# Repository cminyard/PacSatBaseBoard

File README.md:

# PacSatBaseBoard

This is a base board design to start with for a PacSat design, or
really any Pumpkin Space CSKB board.

To use this, pull this project up in KiCad, then do "Save As" under
the file menu and save it in a new directory to use as the starting
point for your board.  You might have to deal with the .git directory
being copied.

All local footprints go into the "footprints" directory, create symbol
libraries in the "symbols" directory as necessary.  There are already
connectors added to those.

NOTE: The CSKB standard has ESQ-126-39-G-D PC104 connectors, which
have 12.19mm pins.  This leaves around 3mm of pin exposed between the
boards.  This design has ESQ-126-38-G-D PC104 connectors, which has
7.36mm pins.  This leaves the 11.05mm as the board height, and 11.11mm
(.438") spacers are pretty common.

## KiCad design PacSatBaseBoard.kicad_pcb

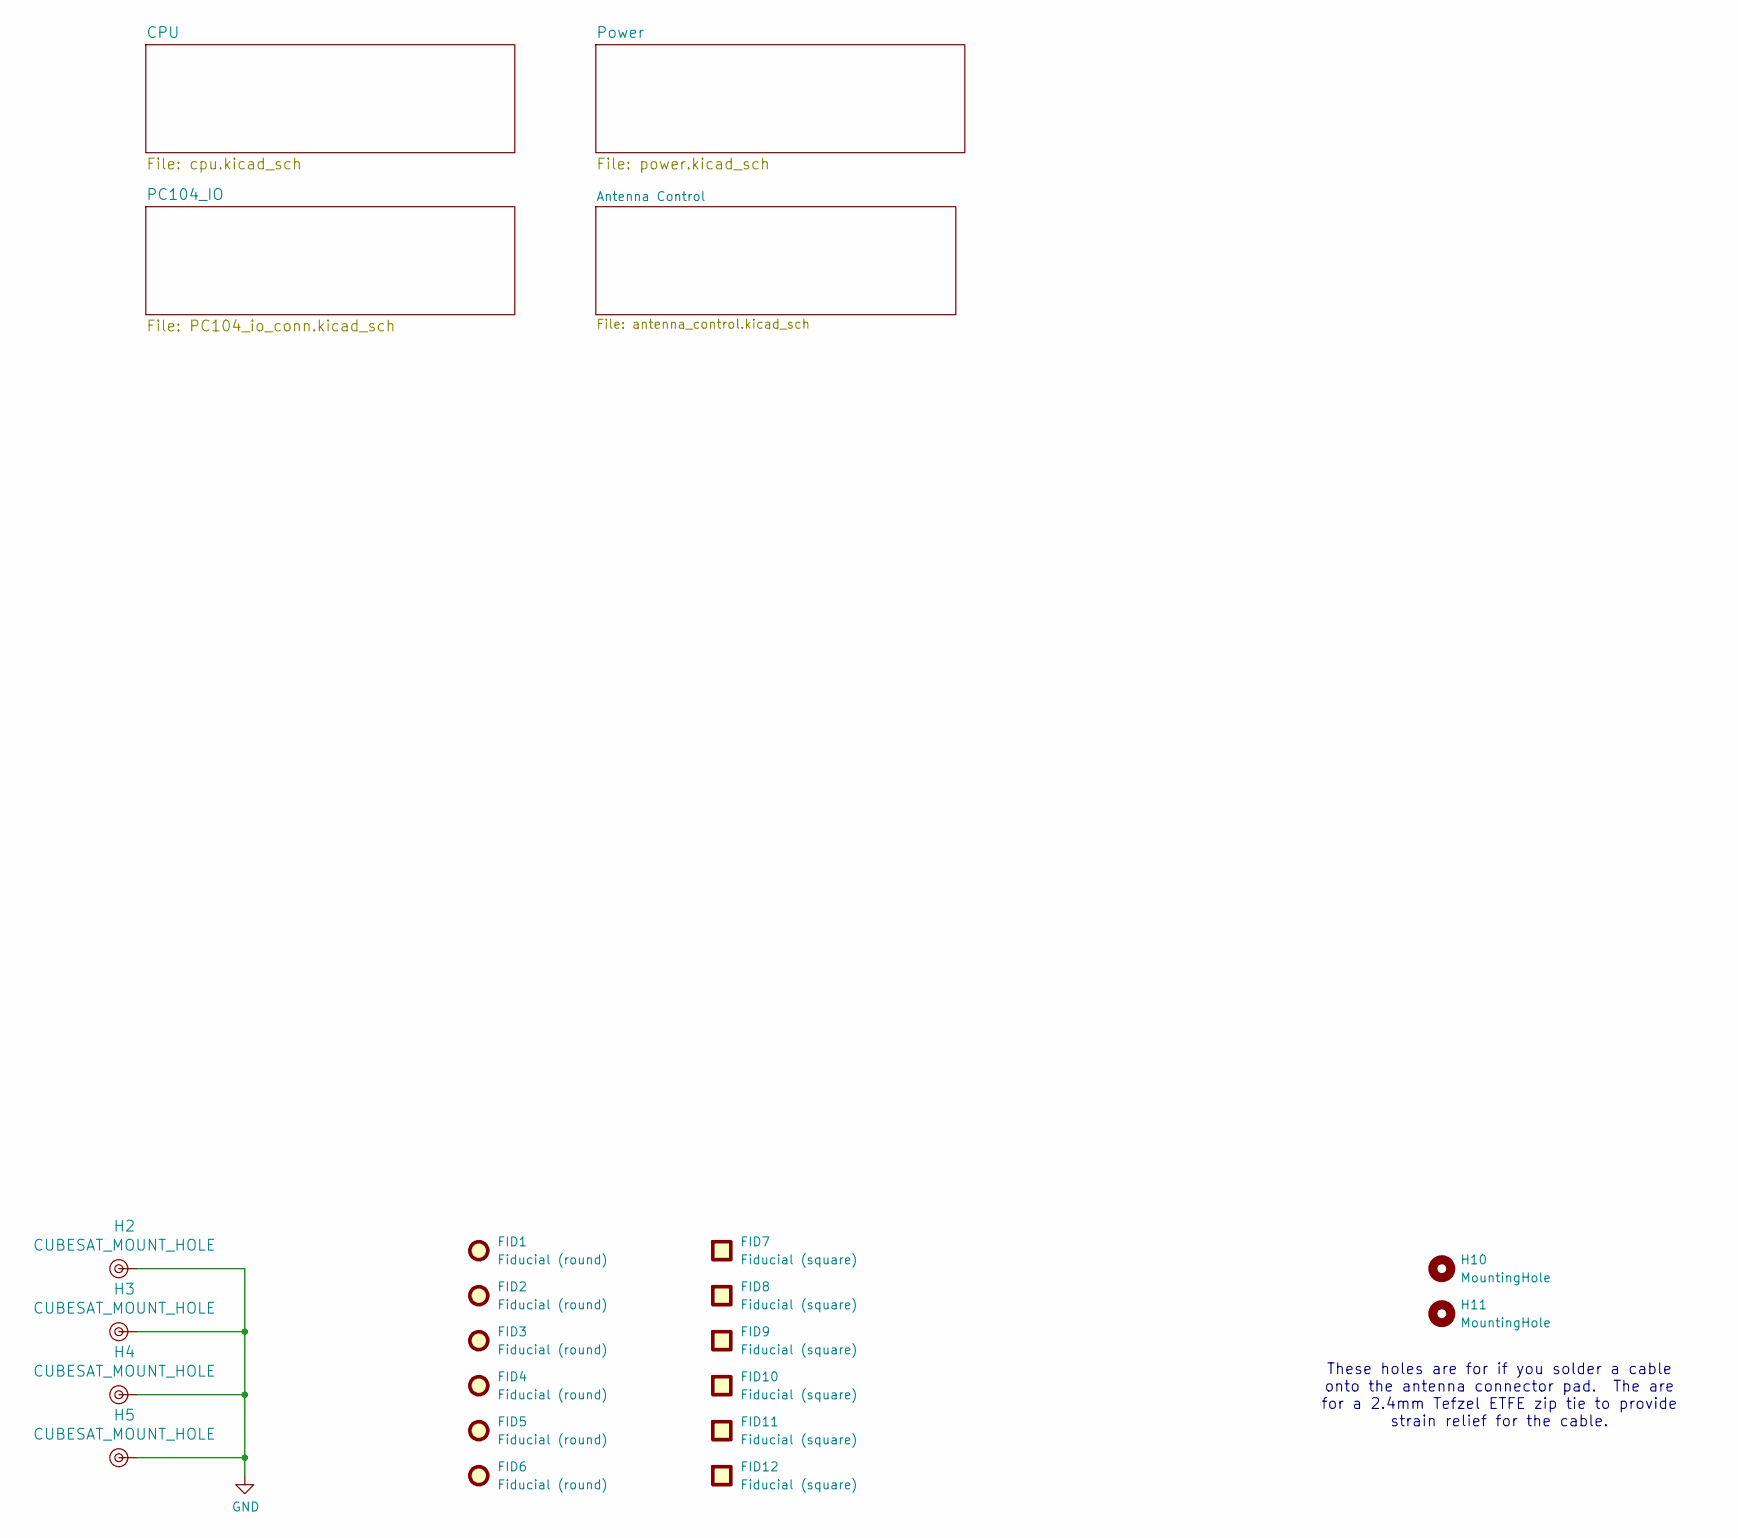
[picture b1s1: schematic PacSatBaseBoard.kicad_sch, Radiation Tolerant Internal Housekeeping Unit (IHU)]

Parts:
FID1, FID2, FID3, FID4, FID5, FID6: Fiducial (round); Fiducial_1mm_Mask2mm
FID7, FID8, FID9, FID10, FID11, FID12: Fiducial (square); Fiducial_Square_1mm_Mask2mm
H2, H3, H4, H5: CUBESAT_MOUNT_HOLE
H10, H11: MountingHole; MountingHole_2.7mm

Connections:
GND: H2.1, H3.1, H4.1, H5.1; also elsewhere on the board

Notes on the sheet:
These holes are for if you solder a cable onto the antenna connector pad. The are for a 2.4mm Tefzel ETFE zip tie to provide strain relief for the cable.

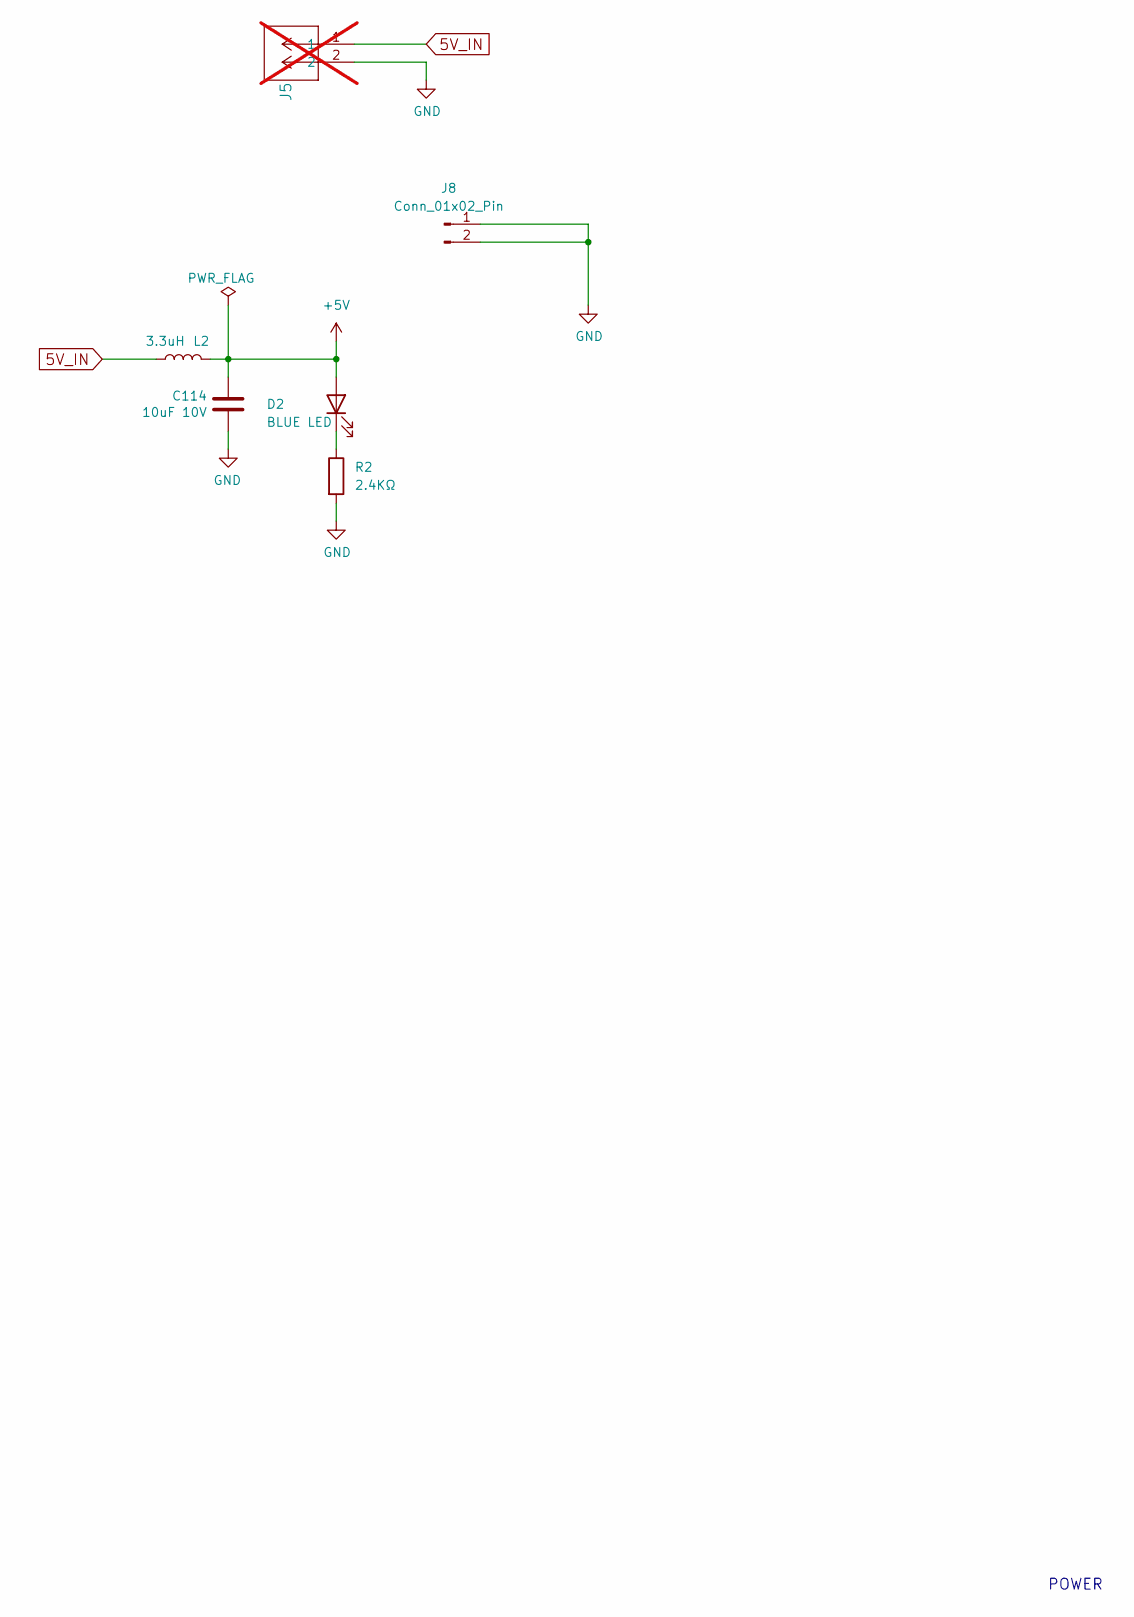
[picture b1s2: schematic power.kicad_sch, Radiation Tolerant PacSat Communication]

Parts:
C114: 10uF 10V; C_1206_3216Metric
D2: BLUE LED; LED_0603_1608Metric_Pad1.05x0.95mm_HandSolder
J5: HTSW-102-07-G-S; CON2_1X2_TU_TSW; not fitted
J8: Conn_01x02_Pin; SolderWire-0.5sqmm_1x02_P4.6mm_D0.9mm_OD2.1mm
L2: 3.3uH; L_1210_3225Metric_Pad1.42x2.65mm_HandSolder
R2: 2.4KΩ; R_0603_1608Metric_Pad0.98x0.95mm_HandSolder

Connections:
5V_IN: J5.1, L2.2; also elsewhere on the board
+5V: C114.1, D2.2 (A), L2.1
GND: C114.2, J5.2, J8.1, J8.2, R2.2; also elsewhere on the board
unnamed: D2.1 (K), R2.1

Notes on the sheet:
POWER

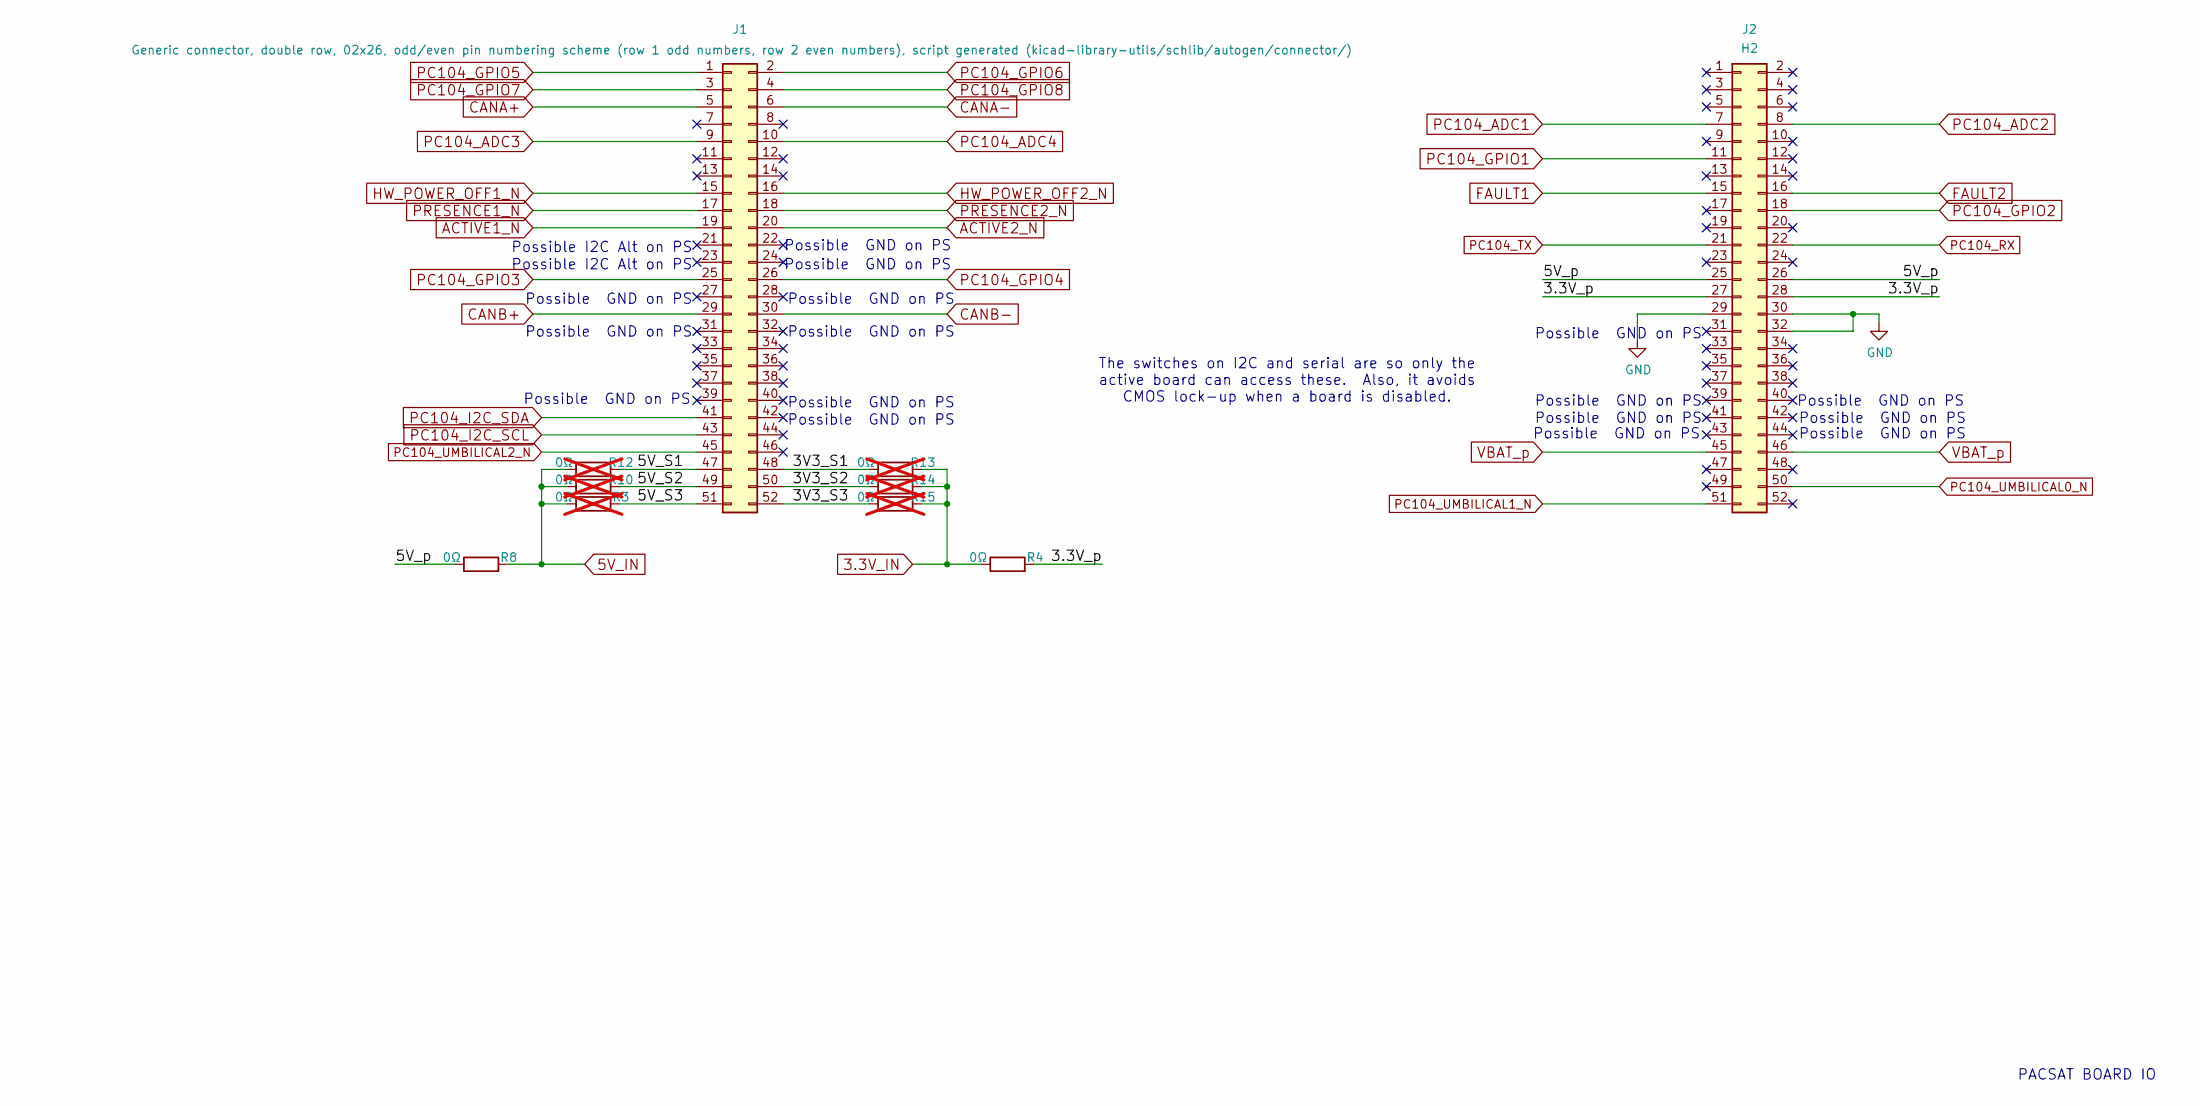
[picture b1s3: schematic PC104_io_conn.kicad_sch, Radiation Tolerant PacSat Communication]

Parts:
J1, J2: ESQ-126-38-G-D; CONN_ESQ-126-39-G-D_SAI
R3, R10, R12, R13, R14, R15: 0Ω; R_0603_1608Metric_Pad0.98x0.95mm_HandSolder; not fitted
R4, R8: 0Ω; R_0603_1608Metric_Pad0.98x0.95mm_HandSolder

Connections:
3.3V_IN: R4.1, R13.2, R14.2, R15.2
5V_IN: R3.1, R8.2, R10.1, R12.1; also elsewhere on the board
/PC104_IO/3.3V_p: J2.27, J2.28, R4.2
/PC104_IO/3V3_S1: J1.48, R13.1
/PC104_IO/3V3_S2: J1.50, R14.1
/PC104_IO/3V3_S3: J1.52, R15.1
/PC104_IO/5V_S1: J1.47, R12.2
/PC104_IO/5V_S2: J1.49, R10.2
/PC104_IO/5V_S3: J1.51, R3.2
/PC104_IO/5V_p: J2.25, J2.26, R8.1
ACTIVE1_N: J1.19
ACTIVE2_N: J1.20
CANA+: J1.5
CANA-: J1.6
CANB+: J1.29
CANB-: J1.30
FAULT1: J2.15
FAULT2: J2.16
GND: J2.29, J2.30, J2.32; also elsewhere on the board
HW_POWER_OFF1_N: J1.15
HW_POWER_OFF2_N: J1.16
PC104_ADC1: J2.7
PC104_ADC2: J2.8
PC104_ADC3: J1.9
PC104_ADC4: J1.10
PC104_GPIO1: J2.11
PC104_GPIO2: J2.18
PC104_GPIO3: J1.25
PC104_GPIO4: J1.26
PC104_GPIO5: J1.1
PC104_GPIO6: J1.2
PC104_GPIO7: J1.3
PC104_GPIO8: J1.4
PC104_I2C_SCL: J1.43
PC104_I2C_SDA: J1.41
PC104_RX: J2.22
PC104_TX: J2.21
PC104_UMBILICAL0_N: J2.50
PC104_UMBILICAL1_N: J2.51
PC104_UMBILICAL2_N: J1.45
PRESENCE1_N: J1.17
PRESENCE2_N: J1.18
VBAT_p: J2.45, J2.46

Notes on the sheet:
Possible GND on PS
The switches on I2C and serial are so only the active board can access these. Also, it avoids CMOS lock-up when a board is disabled.
PACSAT BOARD IO
Possible I2C Alt on PS

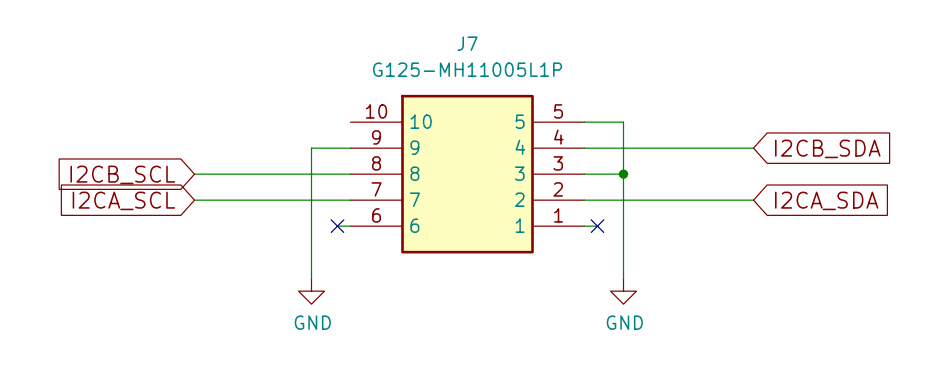
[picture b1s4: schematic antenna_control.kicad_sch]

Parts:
J7: G125-MH11005L1P; Manufacturer_Part_Number G125-MH11005L1P; Mouser Part Number 855-G125-MH11005L1P

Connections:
GND: J7.3, J7.5, J7.9; also elsewhere on the board
I2CA_SCL: J7.7
I2CA_SDA: J7.2
I2CB_SCL: J7.8
I2CB_SDA: J7.4

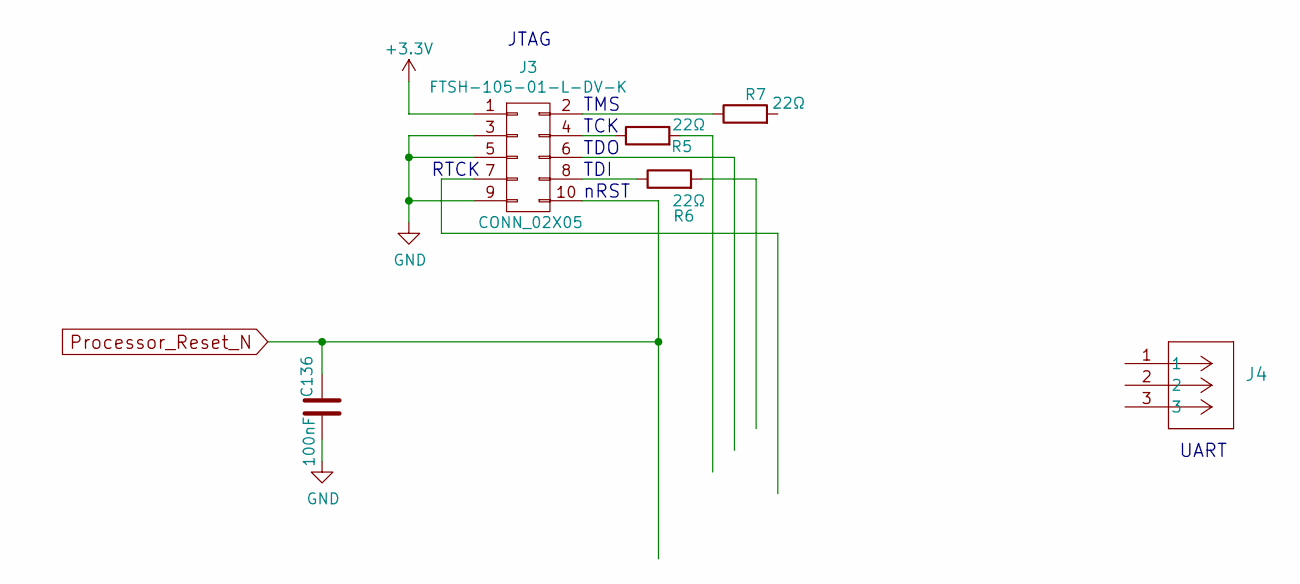
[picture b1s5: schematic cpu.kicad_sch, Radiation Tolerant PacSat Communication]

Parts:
C136: 100nF; C_0402_1005Metric_Pad0.74x0.62mm_HandSolder
J3: FTSH-105-01-L-DV-K
J4: TSW-103-08-F-S-RA; CON3_1X3_TR_TSW_SAI
R5, R6, R7: 22Ω; R_0402_1005Metric_Pad0.72x0.64mm_HandSolder

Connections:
+3.3V: J3.1
GND: C136.2, J3.3, J3.5, J3.9; also elsewhere on the board
unnamed: J3.2, R7.1
unnamed: J3.4, R5.1
unnamed: J3.8, R6.1
Processor_Reset_N: C136.1, J3.10

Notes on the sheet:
RTCK
UART
TCK
nRST
TDI
JTAG
TDO
TMS

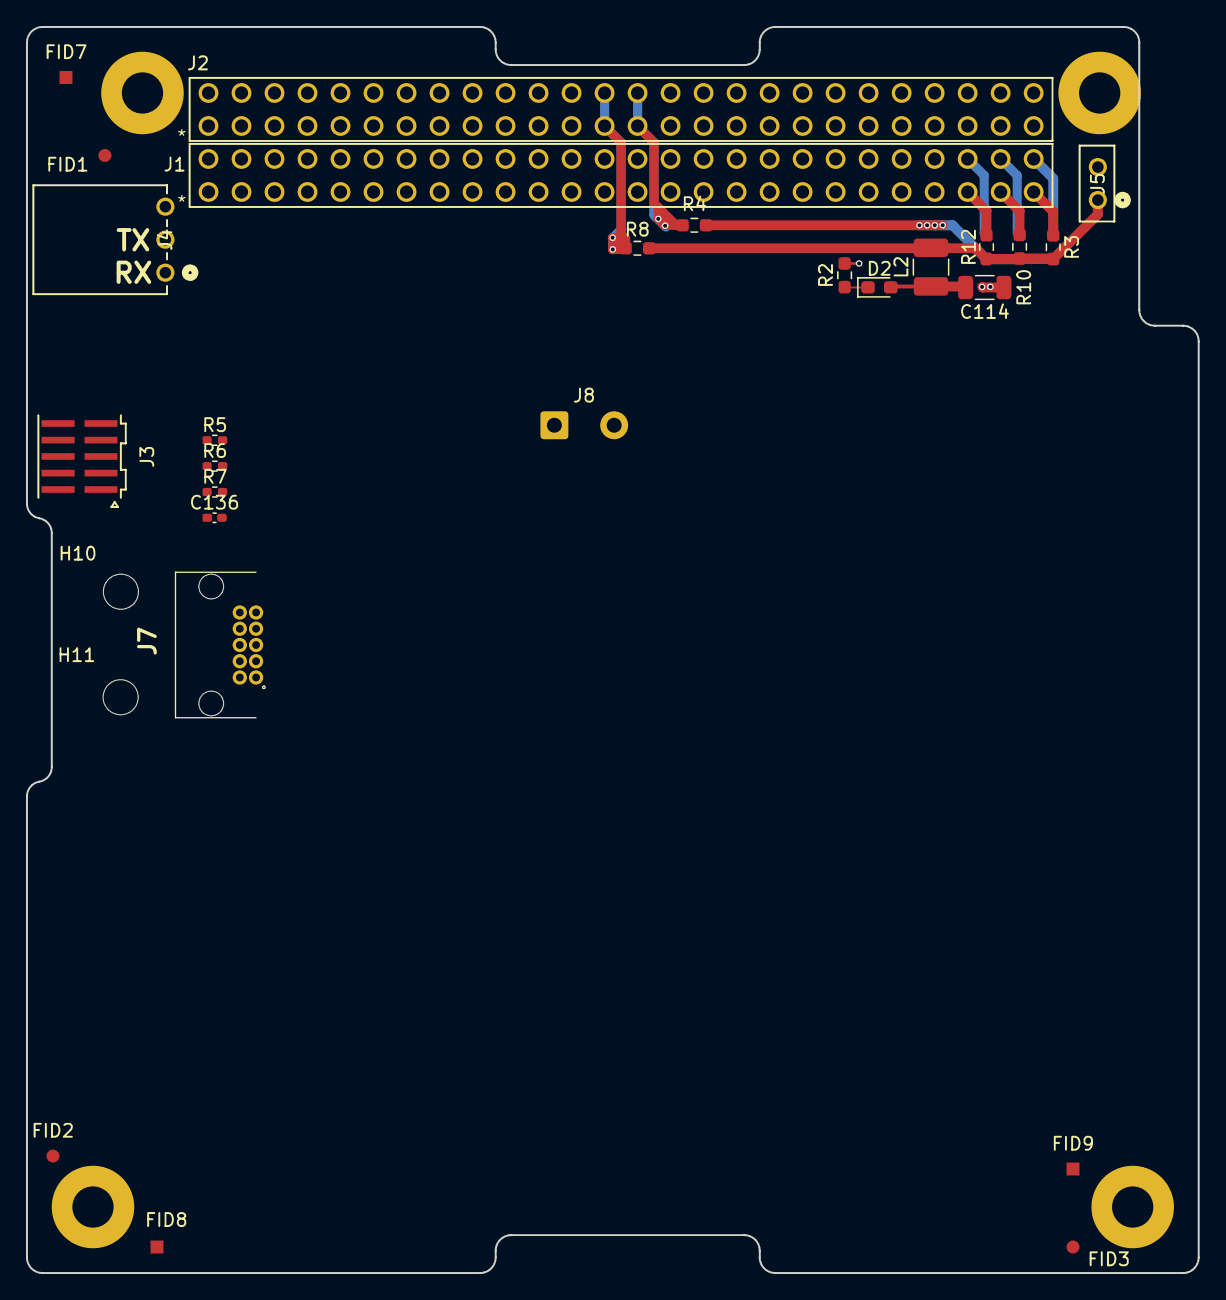
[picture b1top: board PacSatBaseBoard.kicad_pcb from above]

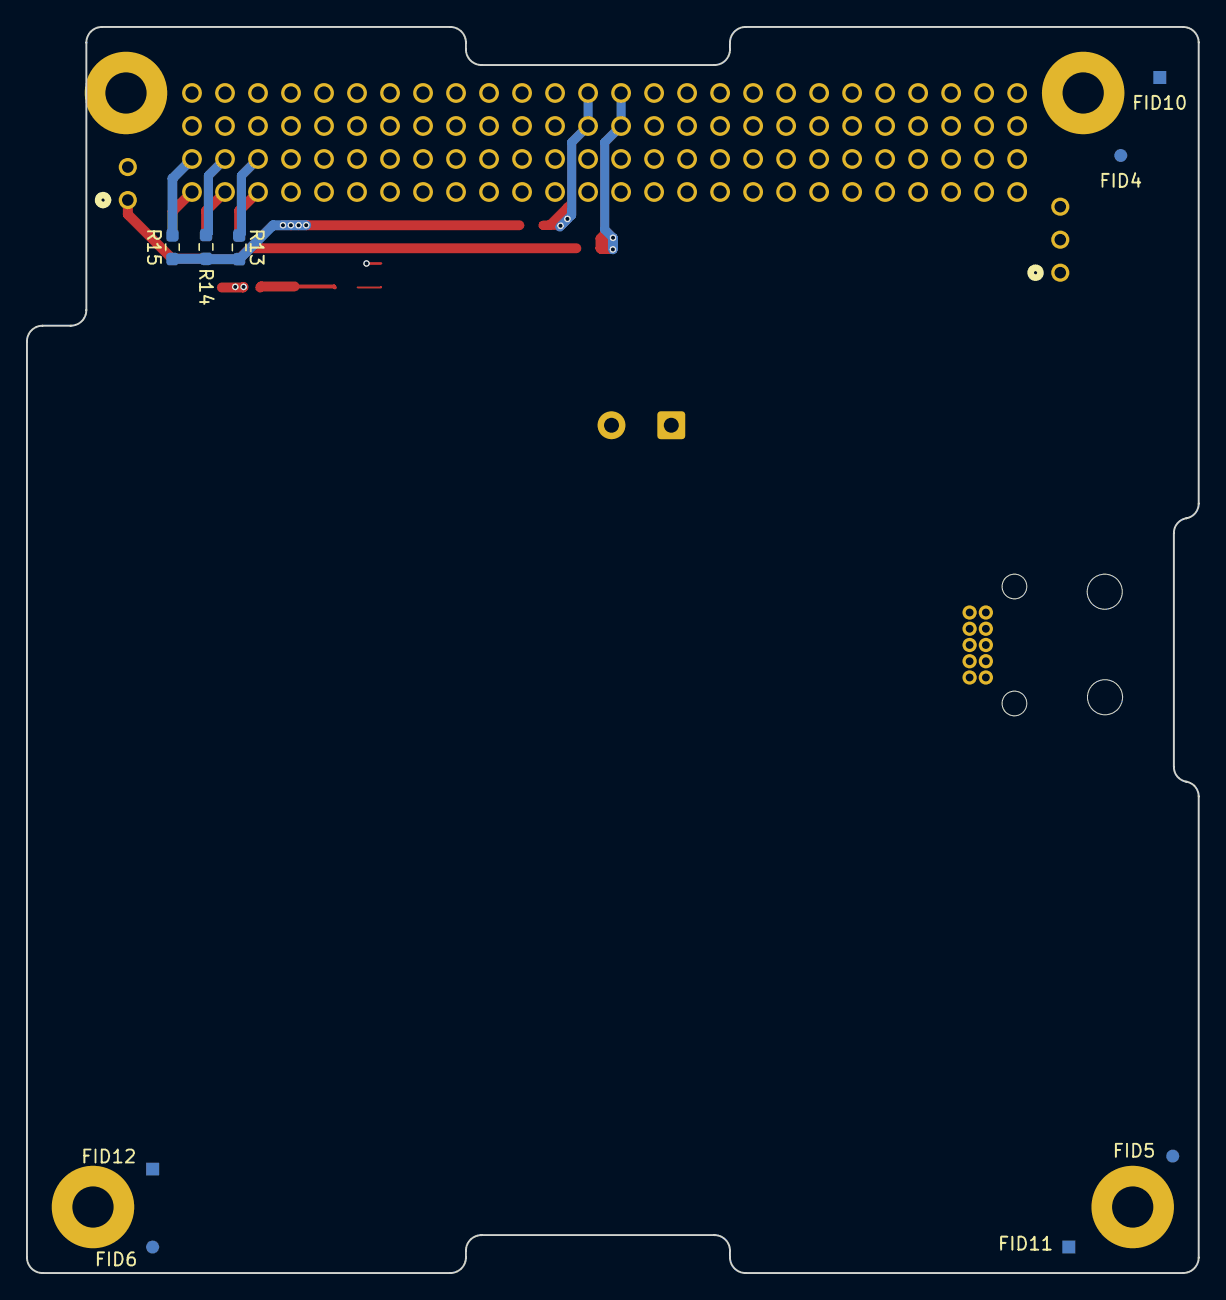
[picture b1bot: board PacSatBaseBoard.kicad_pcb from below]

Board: 6 copper layers, 90.2 x 95.9 mm, 41 parts (9 on the bottom side), 18 nets.

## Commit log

2026-03-20 Initial creation
2026-03-24 Change the connector, power cleanups
    Change the PC104 connector. The CSKB specifies ESQ-126-39-G-D, which
    have 12.19mm pins. This leaves around 3mm of pin exposed between the
    boards. This design has ESQ-126-38-G-D PC104 which will leave no space.
    Rework the power to a fairly common setup.
2026-03-24 Changes from refilling zones
